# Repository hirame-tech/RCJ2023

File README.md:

# README規則
- 基板のバージョンごとの変更点、issue等はboard内の各基板フォルダに書く
- その他仕様等はプログラムが保存されているフォルダ内の一番上の階層に配置されたREADMEに記述する。

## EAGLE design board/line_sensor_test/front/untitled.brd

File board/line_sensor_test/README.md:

## v1 memo
- U1 0~15
- U2 16~29

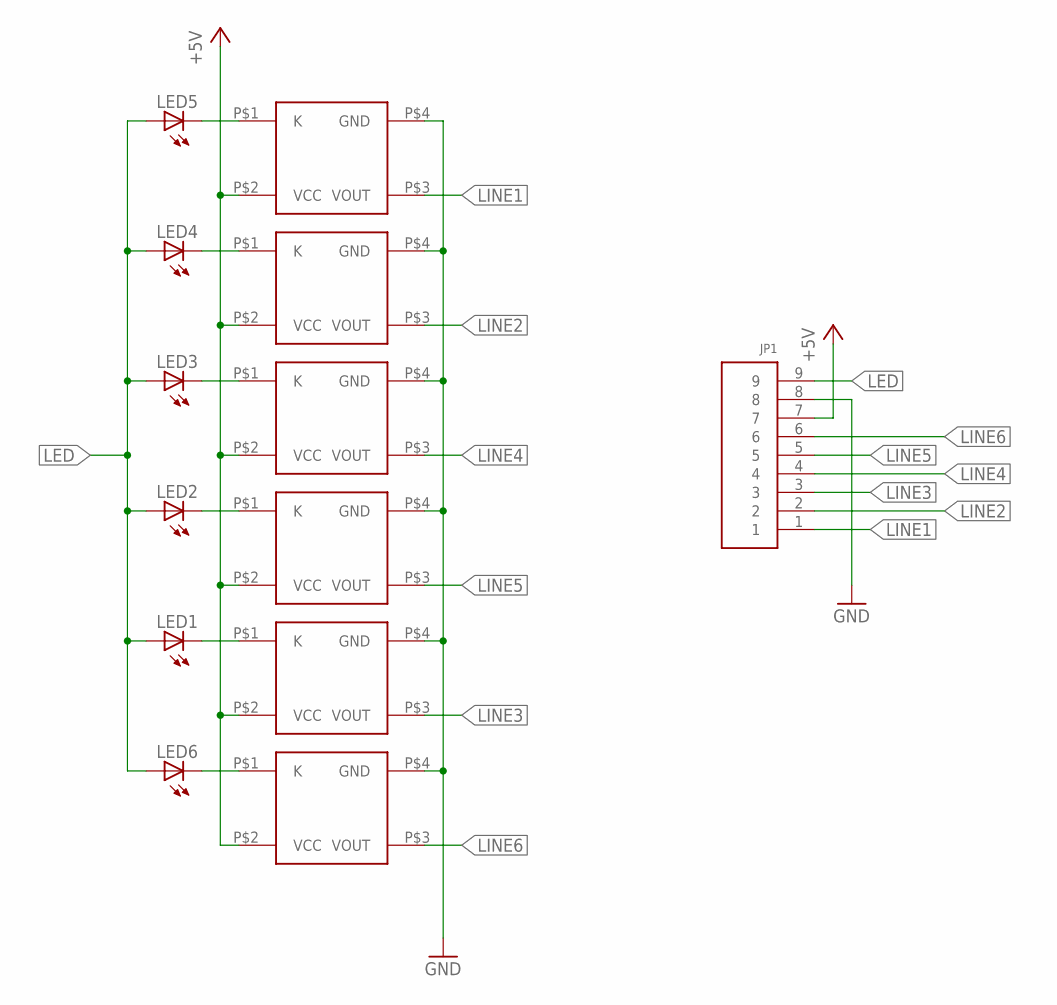
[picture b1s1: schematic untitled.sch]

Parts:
JP1: 9PIN; B9B-PH-K-S
LED1, LED2, LED3, LED4, LED5, LED6: LED5MM
U$1, U$2, U$3, U$4, U$5, U$6: S4282-51

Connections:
+5V: JP1.7, U$1.P$2 (VCC), U$2.P$2 (VCC), U$3.P$2 (VCC), U$4.P$2 (VCC), U$5.P$2 (VCC), U$6.P$2 (VCC)
GND: JP1.8, U$1.P$4 (GND), U$2.P$4 (GND), U$3.P$4 (GND), U$4.P$4 (GND), U$5.P$4 (GND), U$6.P$4 (GND)
LED: JP1.9, LED1.A, LED2.A, LED3.A, LED4.A, LED5.A, LED6.A
LINE1: JP1.1, U$1.P$3 (VOUT)
LINE2: JP1.2, U$2.P$3 (VOUT)
LINE3: JP1.3, U$5.P$3 (VOUT)
LINE4: JP1.4, U$3.P$3 (VOUT)
LINE5: JP1.5, U$4.P$3 (VOUT)
LINE6: JP1.6, U$6.P$3 (VOUT)
unnamed: LED5.K (C), U$1.P$1 (K)
unnamed: LED4.K (C), U$2.P$1 (K)
unnamed: LED3.K (C), U$3.P$1 (K)
unnamed: LED2.K (C), U$4.P$1 (K)
unnamed: LED1.K (C), U$5.P$1 (K)
unnamed: LED6.K (C), U$6.P$1 (K)

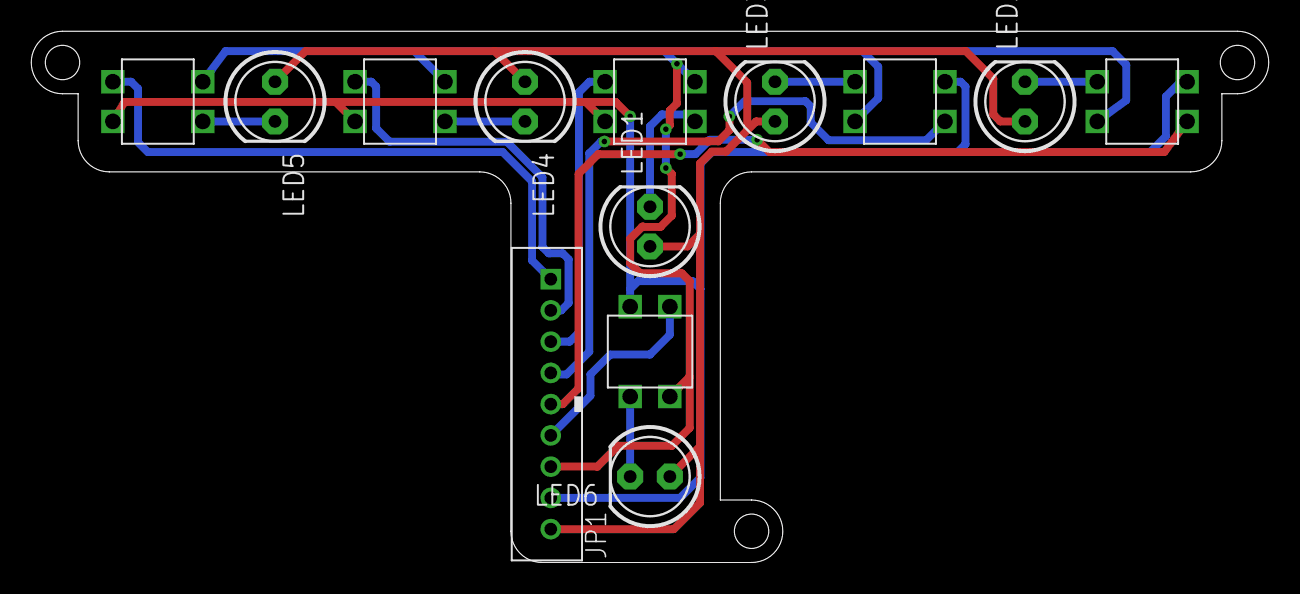
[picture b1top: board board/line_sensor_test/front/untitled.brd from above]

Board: 2 copper layers, 79.2 x 34.0 mm, 13 parts (0 on the bottom side), 15 nets.

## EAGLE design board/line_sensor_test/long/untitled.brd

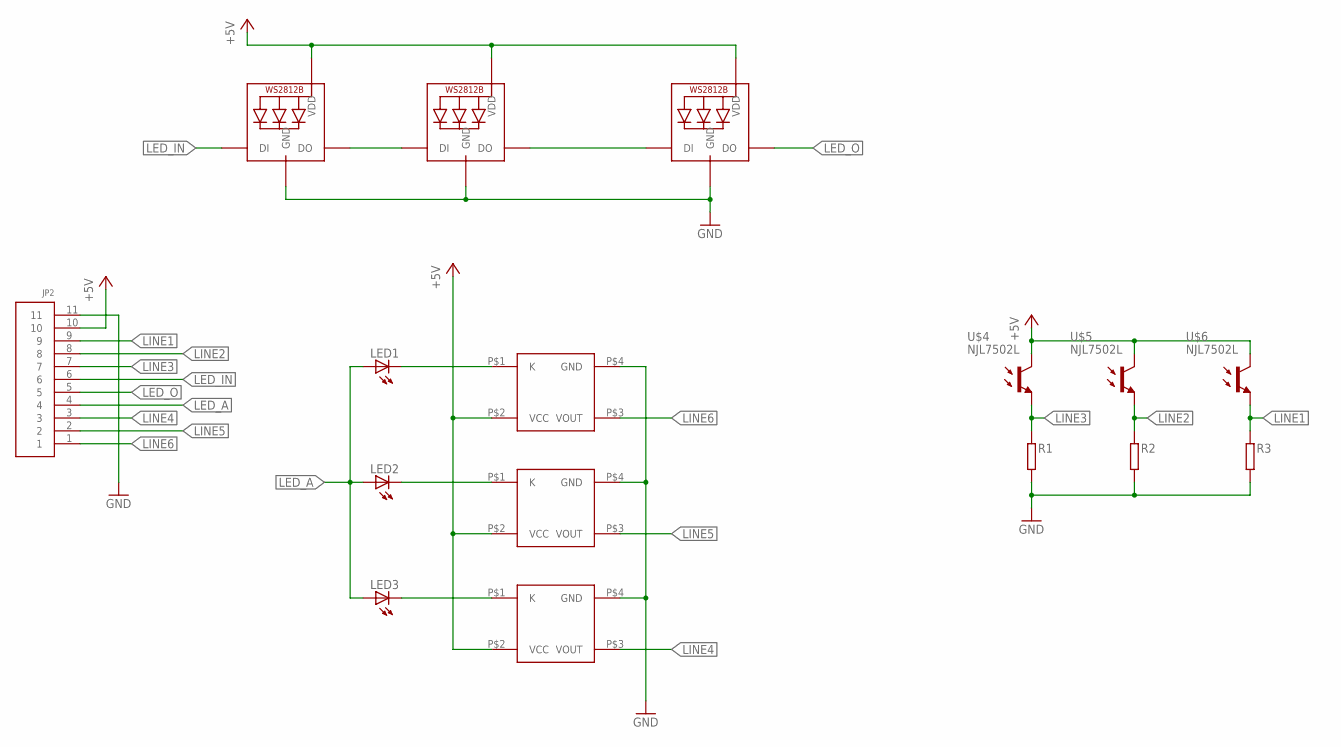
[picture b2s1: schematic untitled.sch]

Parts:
JP2: 11PIN; B11B-PH-K-S
LED1, LED2, LED3: LED5MM
LED4, LED5, LED6: WS2812B_5050N; WS2812B-NARROW
R1, R2, R3: RESISTOR1608; SMD1608
U$1, U$2, U$3: S4282-51
U$4, U$5, U$6: NJL7502L

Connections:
+5V: JP2.10, LED4.1-VDD (VDD), LED5.1-VDD (VDD), LED6.1-VDD (VDD), U$1.P$2 (VCC), U$2.P$2 (VCC), U$3.P$2 (VCC), U$4.C, U$5.C, U$6.C
GND: JP2.11, LED4.3-GND (GND), LED5.3-GND (GND), LED6.3-GND (GND), R1.2, R2.2, R3.2, U$1.P$4 (GND), U$2.P$4 (GND), U$3.P$4 (GND)
LED_A: JP2.4, LED1.A, LED2.A, LED3.A
LED_IN: JP2.6, LED6.4-DIN (DI)
LED_O: JP2.5, LED4.2-DOUT (DO)
LINE1: JP2.9, R3.1, U$6.E
LINE2: JP2.8, R2.1, U$5.E
LINE3: JP2.7, R1.1, U$4.E
LINE4: JP2.3, U$3.P$3 (VOUT)
LINE5: JP2.2, U$2.P$3 (VOUT)
LINE6: JP2.1, U$1.P$3 (VOUT)
unnamed: LED1.K (C), U$1.P$1 (K)
unnamed: LED2.K (C), U$2.P$1 (K)
unnamed: LED3.K (C), U$3.P$1 (K)
unnamed: LED5.4-DIN (DI), LED6.2-DOUT (DO)
unnamed: LED4.4-DIN (DI), LED5.2-DOUT (DO)

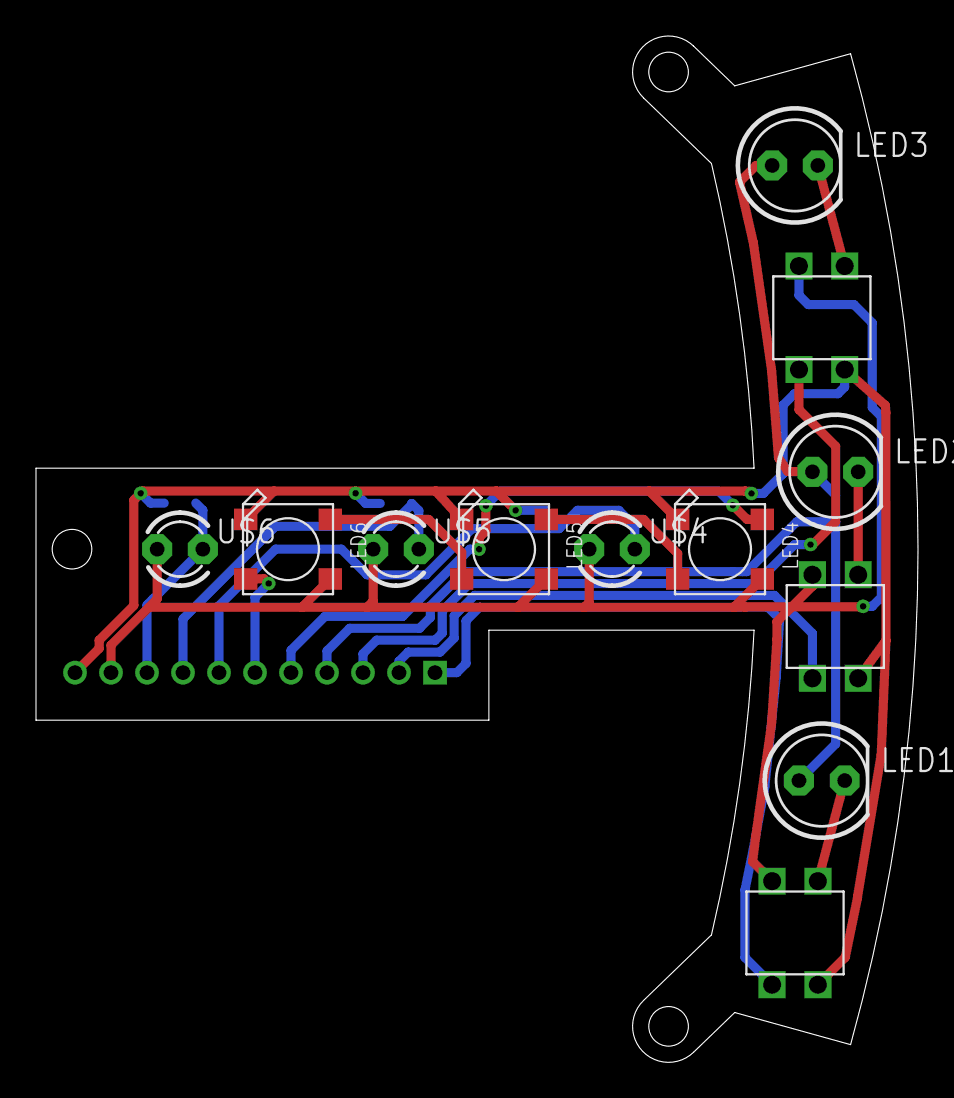
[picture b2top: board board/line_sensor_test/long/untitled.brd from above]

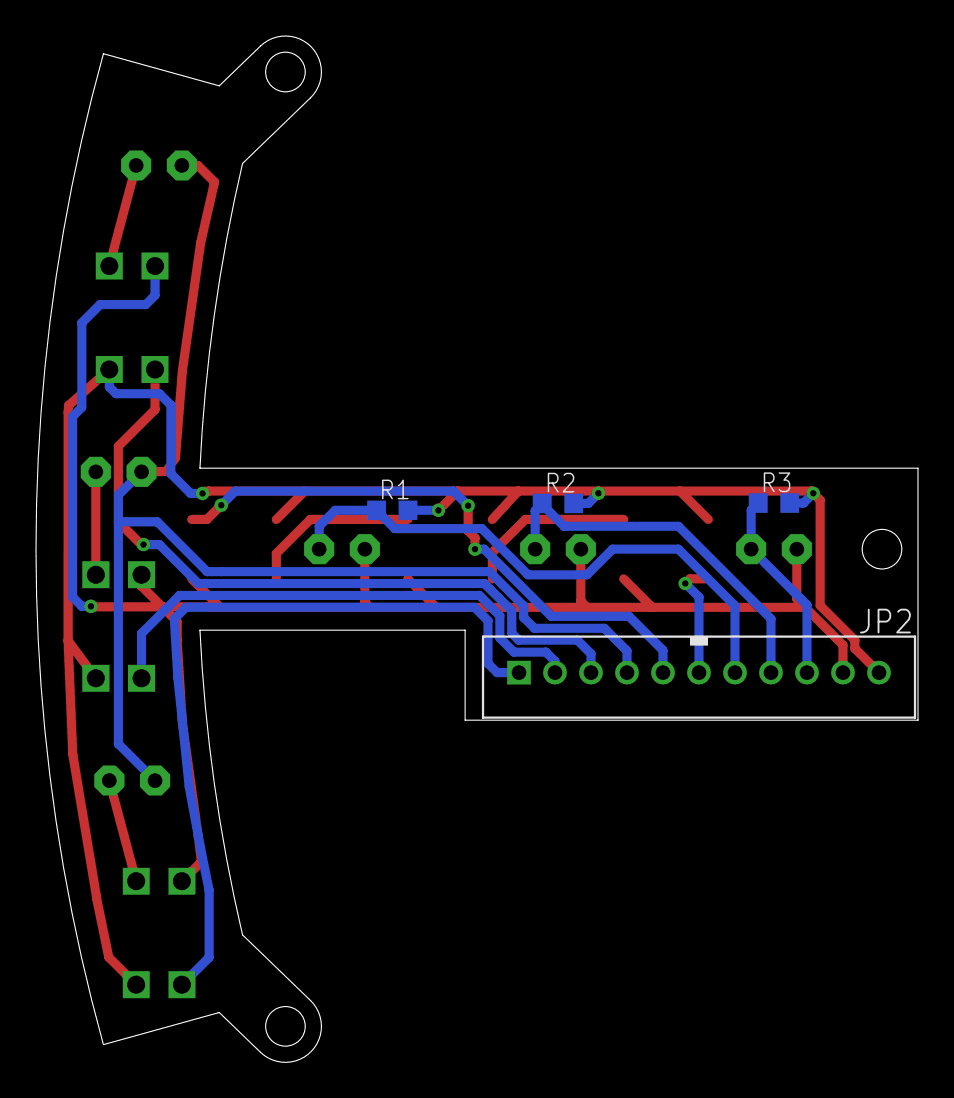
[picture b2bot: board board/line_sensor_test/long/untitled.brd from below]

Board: 2 copper layers, 49.0 x 57.0 mm, 16 parts (4 on the bottom side), 16 nets.

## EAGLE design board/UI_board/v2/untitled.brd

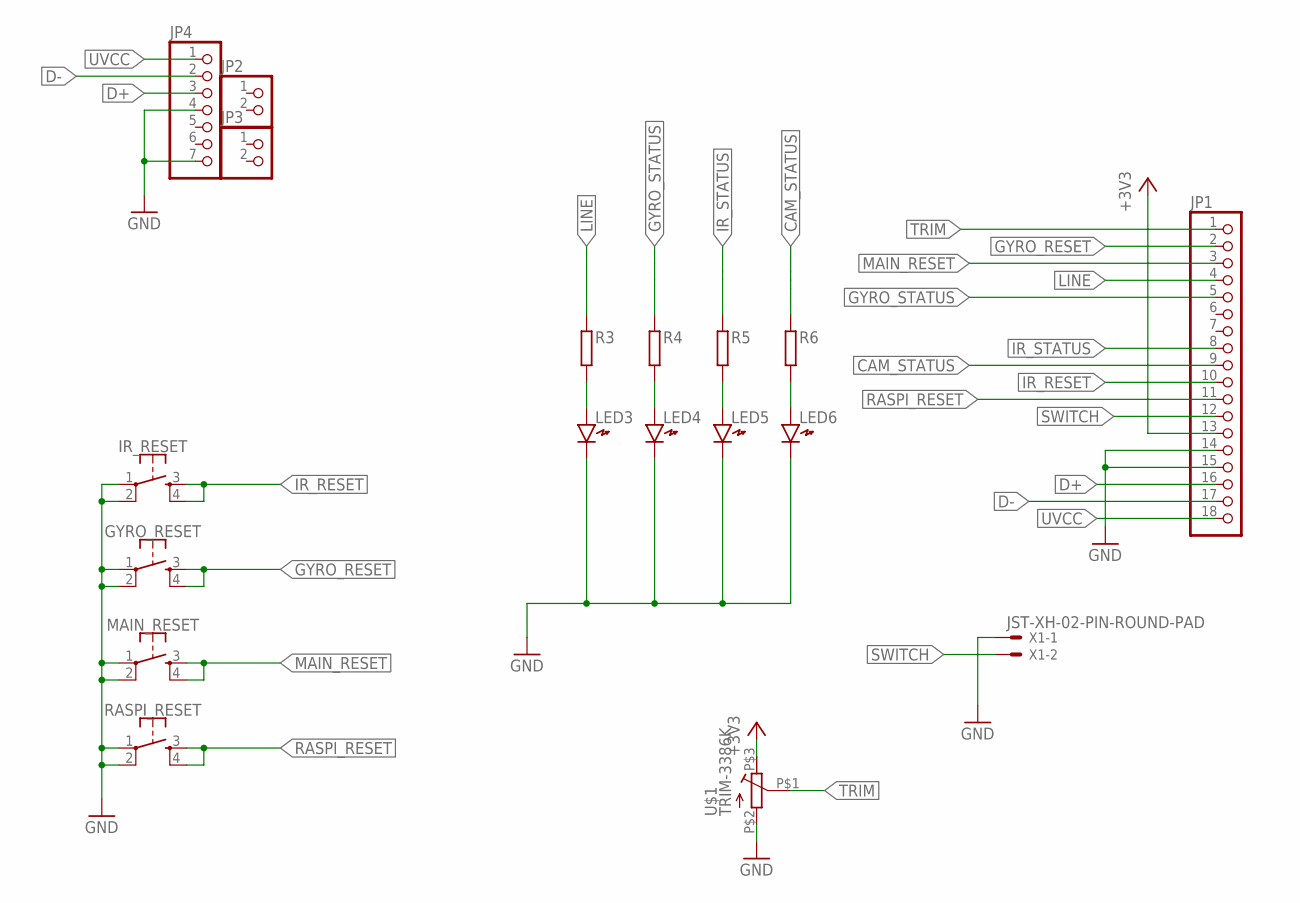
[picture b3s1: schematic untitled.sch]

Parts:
GYRO_RESET: MOMENTARY-SWITCH-SPST-2-SMD-5.2MM; TACTILE_SWITCH_SMD_5.2MM
IR_RESET: MOMENTARY-SWITCH-SPST-2-SMD-5.2MM; TACTILE_SWITCH_SMD_5.2MM
JP1: PINHD-1X18; 1X18
JP2, JP3: PINHD-1X2; 1X02
JP4: PINHD-1X7; 1X07
LED3, LED4, LED5, LED6: LED1608
MAIN_RESET: MOMENTARY-SWITCH-SPST-2-SMD-5.2MM; TACTILE_SWITCH_SMD_5.2MM
R3, R4, R5, R6: RESISTOR1608; SMD1608
RASPI_RESET: MOMENTARY-SWITCH-SPST-2-SMD-5.2MM; TACTILE_SWITCH_SMD_5.2MM
U$1: TRIM-3386K
X1: JST-XH-02-PIN-ROUND-PAD; JST-XH-02-PACKAGE-ROUND-PAD

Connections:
+3V3: JP1.13, U$1.P$3 (1)
CAM_STATUS: JP1.9, R6.1
D+: JP1.16, JP4.3
D-: JP1.17, JP4.2
GND: GYRO_RESET.1, GYRO_RESET.2, IR_RESET.1, IR_RESET.2, JP1.14, JP1.15, JP4.4, JP4.7, LED3.K, LED4.K, LED5.K, LED6.K, MAIN_RESET.1, MAIN_RESET.2, RASPI_RESET.1, RASPI_RESET.2, U$1.P$2 (2), X1.1
GYRO_RESET: GYRO_RESET.3, GYRO_RESET.4, JP1.2
GYRO_STATUS: JP1.5, R4.1
IR_RESET: IR_RESET.3, IR_RESET.4, JP1.10
IR_STATUS: JP1.8, R5.1
LINE: JP1.4, R3.1
MAIN_RESET: JP1.3, MAIN_RESET.3, MAIN_RESET.4
unnamed: LED3.A, R3.2
unnamed: LED4.A, R4.2
unnamed: LED5.A, R5.2
unnamed: LED6.A, R6.2
RASPI_RESET: JP1.11, RASPI_RESET.3, RASPI_RESET.4
SWITCH: JP1.12, X1.2
TRIM: JP1.1, U$1.P$1 (3)
UVCC: JP1.18, JP4.1

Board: 2 copper layers, 18 parts (0 on the bottom side), 19 nets, no tracks yet.

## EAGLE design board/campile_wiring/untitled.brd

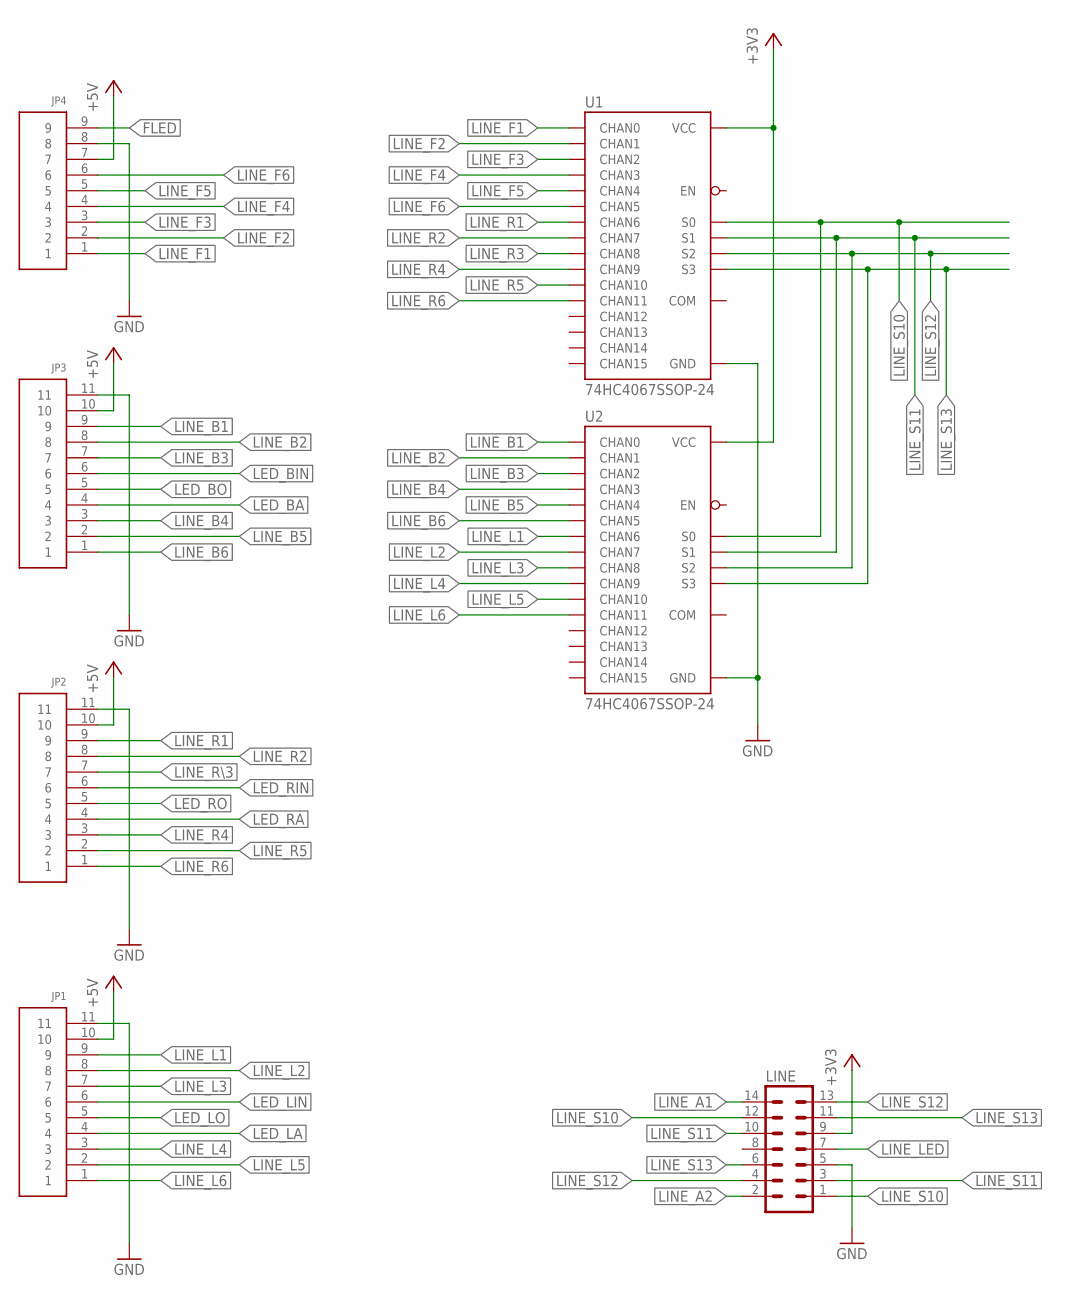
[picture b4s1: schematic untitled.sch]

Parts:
JP1, JP2, JP3: 11PIN; B11B-PH-K-S
JP4: 9PIN; B9B-PH-K-S
LINE: MA07-2
U1, U2: 74HC4067SSOP-24; SSOP24

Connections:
+3V3: LINE.9, U1.24 (VCC), U2.24 (VCC)
+5V: JP1.10, JP2.10, JP3.10, JP4.7
FLED: JP4.9
GND: JP1.11, JP2.11, JP3.11, JP4.8, LINE.5, U1.12 (GND), U2.12 (GND)
LED_BA: JP3.4
LED_BIN: JP3.6
LED_BO: JP3.5
LED_LA: JP1.4
LED_LIN: JP1.6
LED_LO: JP1.5
LED_RA: JP2.4
LED_RIN: JP2.6
LED_RO: JP2.5
LINE_A1: LINE.14
LINE_A2: LINE.2
LINE_B1: JP3.9, U2.9 (CHAN0)
LINE_B2: JP3.8, U2.8 (CHAN1)
LINE_B3: JP3.7, U2.7 (CHAN2)
LINE_B4: JP3.3, U2.6 (CHAN3)
LINE_B5: JP3.2, U2.5 (CHAN4)
LINE_B6: JP3.1, U2.4 (CHAN5)
LINE_F1: JP4.1, U1.9 (CHAN0)
LINE_F2: JP4.2, U1.8 (CHAN1)
LINE_F3: JP4.3, U1.7 (CHAN2)
LINE_F4: JP4.4, U1.6 (CHAN3)
LINE_F5: JP4.5, U1.5 (CHAN4)
LINE_F6: JP4.6, U1.4 (CHAN5)
LINE_L1: JP1.9, U2.3 (CHAN6)
LINE_L2: JP1.8, U2.2 (CHAN7)
LINE_L3: JP1.7, U2.23 (CHAN8)
LINE_L4: JP1.3, U2.22 (CHAN9)
LINE_L5: JP1.2, U2.21 (CHAN10)
LINE_L6: JP1.1, U2.20 (CHAN11)
LINE_LED: LINE.7
LINE_R1: JP2.9, U1.3 (CHAN6)
LINE_R2: JP2.8, U1.2 (CHAN7)
LINE_R3: U1.23 (CHAN8)
LINE_R4: JP2.3, U1.22 (CHAN9)
LINE_R5: JP2.2, U1.21 (CHAN10)
LINE_R6: JP2.1, U1.20 (CHAN11)
LINE_R\3: JP2.7
LINE_S10: LINE.1, LINE.12, U1.10 (S0), U2.10 (S0)
LINE_S11: LINE.3, LINE.10, U1.11 (S1), U2.11 (S1)
LINE_S12: LINE.4, LINE.13, U1.14 (S2), U2.14 (S2)
LINE_S13: LINE.6, LINE.11, U1.13 (S3), U2.13 (S3)

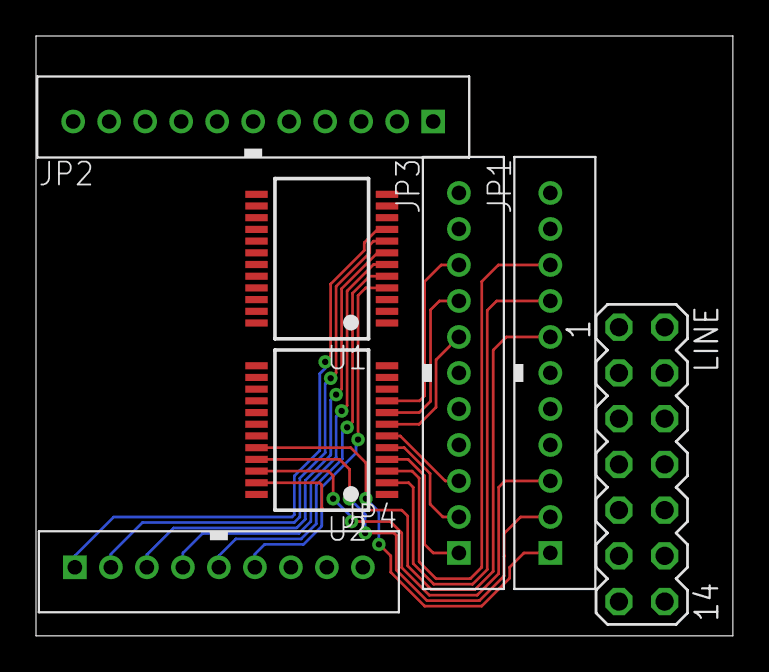
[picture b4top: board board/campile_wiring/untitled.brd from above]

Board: 2 copper layers, 38.7 x 33.3 mm, 7 parts (0 on the bottom side), 30 nets.

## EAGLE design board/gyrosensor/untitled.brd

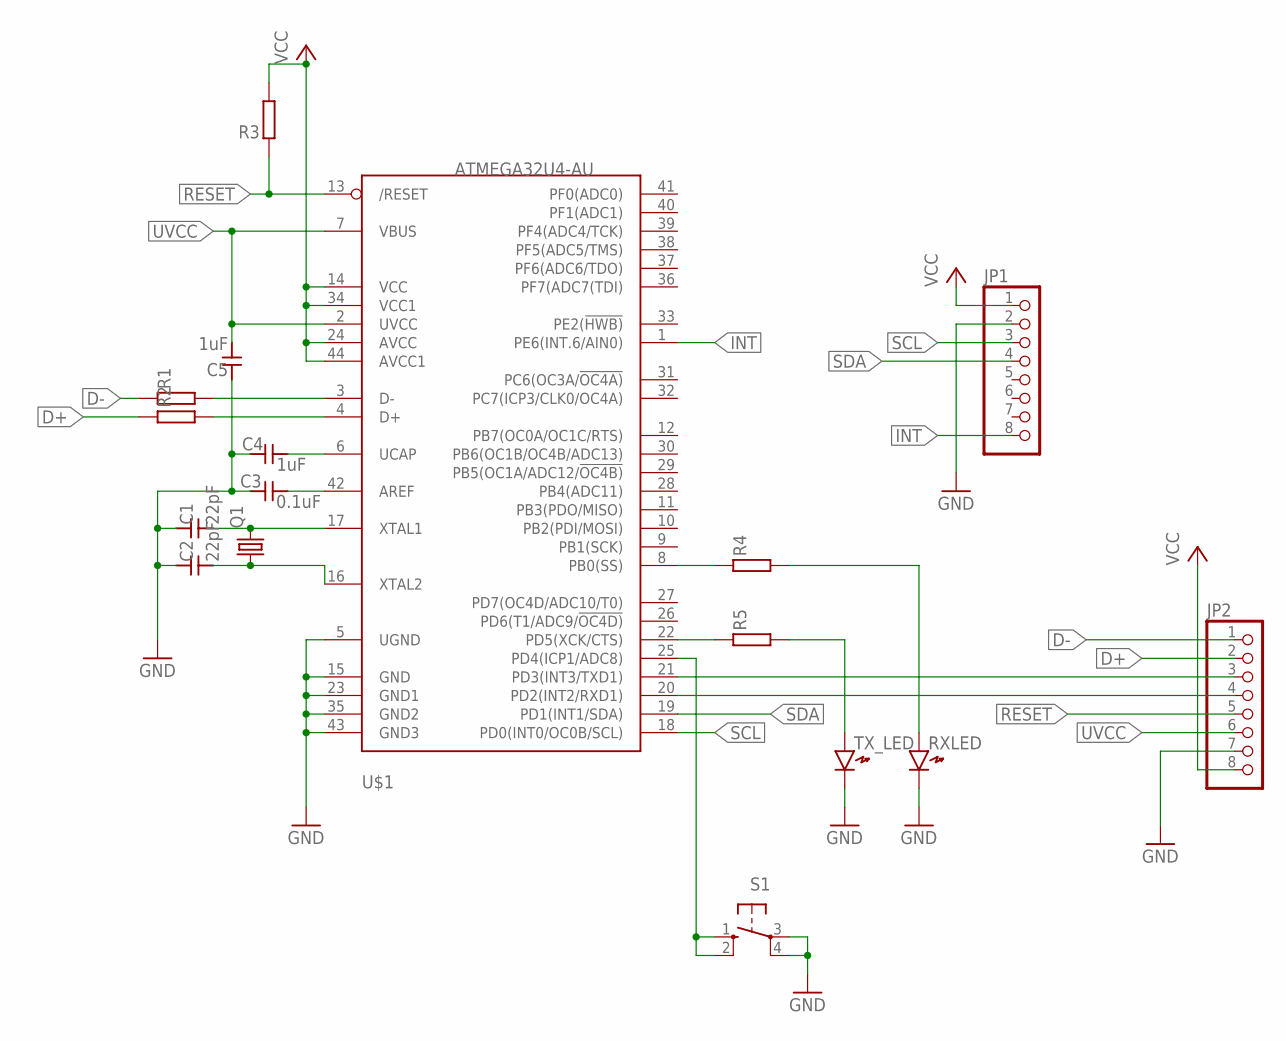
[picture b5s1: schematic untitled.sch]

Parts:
C1, C2: 22pF; SMD1608
C3: 0.1uF; SMD1608
C4, C5: 1uF; SMD1608
JP1, JP2: PINHD-1X8; 1X08
Q1: CRYSTALHC49S; HC49/S
R1, R2, R3, R4, R5: RESISTOR1608; SMD1608
RXLED: LED1608
S1: 10-XX; B3F-10XX
TX_LED: LED1608
U$1: ATMEGA32U4-AU; TQFP44

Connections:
D+: JP2.2, R2.1
D-: JP2.1, R1.1
GND: C1.1, C2.1, C3.1, C4.1, C5.1, JP1.2, JP2.7, RXLED.K, S1.3, S1.4 (P1), TX_LED.K, U$1.5 (UGND), U$1.15 (GND), U$1.23 (GND1), U$1.35 (GND2), U$1.43 (GND3)
INT: JP1.8, U$1.1 (PE6(INT.6/AIN0))
unnamed: C1.2, Q1.2, U$1.17 (XTAL1)
unnamed: C2.2, Q1.1, U$1.16 (XTAL2)
unnamed: C4.2, U$1.6 (UCAP)
unnamed: C3.2, U$1.42 (AREF)
unnamed: S1.1 (S), S1.2 (S1), U$1.25 (PD4(ICP1/ADC8))
unnamed: R4.1, U$1.8 (PB0(SS))
unnamed: R5.1, U$1.22 (PD5(XCK/CTS))
unnamed: R1.2, U$1.3 (D-)
unnamed: R2.2, U$1.4 (D+)
unnamed: R5.2, TX_LED.A
unnamed: R4.2, RXLED.A
unnamed: JP2.3, U$1.21 (PD3(INT3/TXD1))
unnamed: JP2.4, U$1.20 (PD2(INT2/RXD1))
RESET: JP2.5, R3.1, U$1.13 (/RESET)
SCL: JP1.3, U$1.18 (PD0(INT0/OC0B/SCL))
SDA: JP1.4, U$1.19 (PD1(INT1/SDA))
UVCC: C5.2, JP2.6, U$1.2 (UVCC), U$1.7 (VBUS)
VCC: JP1.1, JP2.8, R3.2, U$1.14 (VCC), U$1.24 (AVCC), U$1.34 (VCC1), U$1.44 (AVCC1)

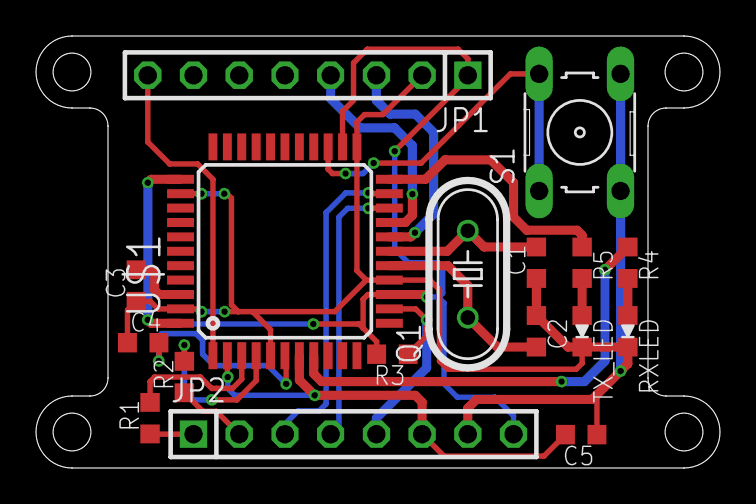
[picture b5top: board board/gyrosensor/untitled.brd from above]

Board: 2 copper layers, 38.0 x 24.0 mm, 17 parts (0 on the bottom side), 22 nets.

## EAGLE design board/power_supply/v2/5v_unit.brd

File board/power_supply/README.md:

## power supply board v1
- OKLを手はんだに対応させた方がいいのでは？
- ヒューズの長さが違う

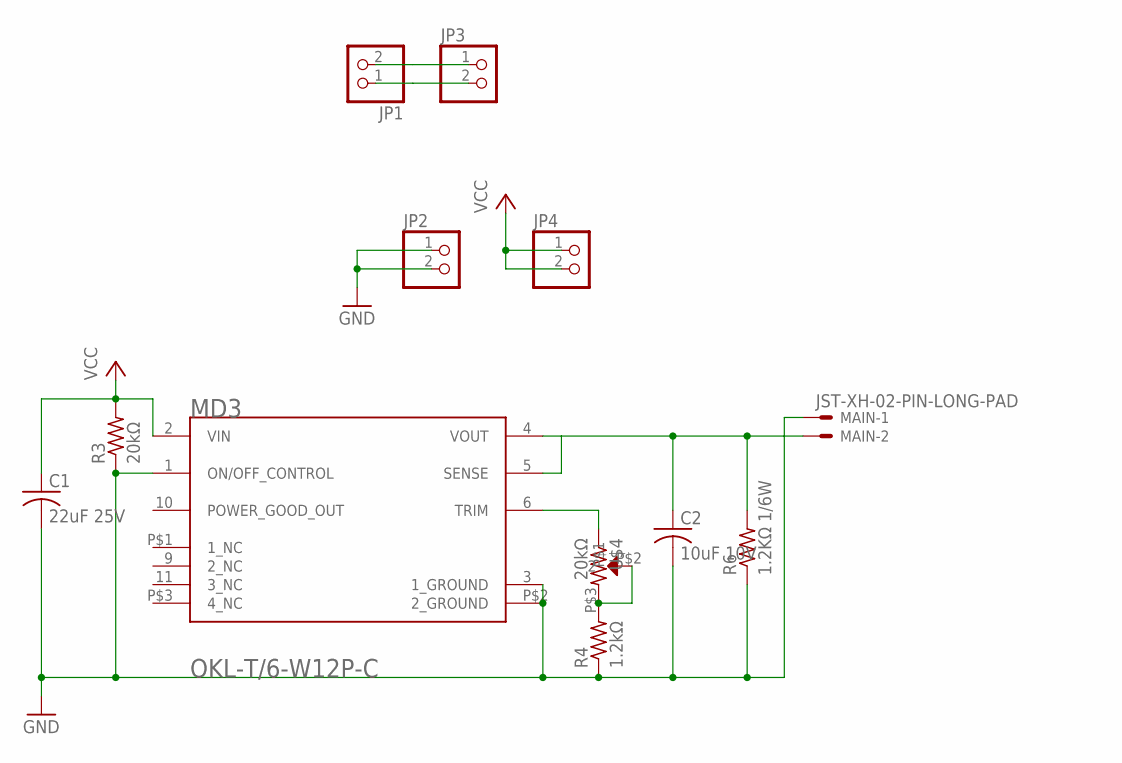
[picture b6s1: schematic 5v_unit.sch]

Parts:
C1: 22uF 25V; C2012
C2: 10uF 10V; C2012
JP1, JP2, JP3, JP4: PINHD-1X2; 1X02
MAIN: JST-XH-02-PIN-LONG-PAD; JST-XH-02-PACKAGE-LONG-PAD
MD3: OKL-T/6-W12P-CMURATA_OKL-T-6-W12P-C_0_0; MURATA_OKL-T-6-W12P-C_0
R3: 20kΩ; M2012
R4: 1.2kΩ; M2012
R6: 1.2KΩ 1/6W; 0805-THM
U$4: 20kΩ; R-TRIM

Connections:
GND: C1.2, C2.2, JP2.1, JP2.2, MAIN.1, MD3.1 (ON/OFF_CONTROL), MD3.3 (1_GROUND), MD3.P$2 (2_GROUND), R3.1, R4.1, R6.1
unnamed: JP1.1, JP1.2, JP3.1, JP3.2
unnamed: R4.2, U$4.P$2 (2), U$4.P$3
unnamed: C2.1, MAIN.2, MD3.4 (VOUT), MD3.5 (SENSE), R6.2
unnamed: MD3.6 (TRIM), U$4.P$1 (1)
VCC: C1.1, JP4.1, JP4.2, MD3.2 (VIN), R3.2

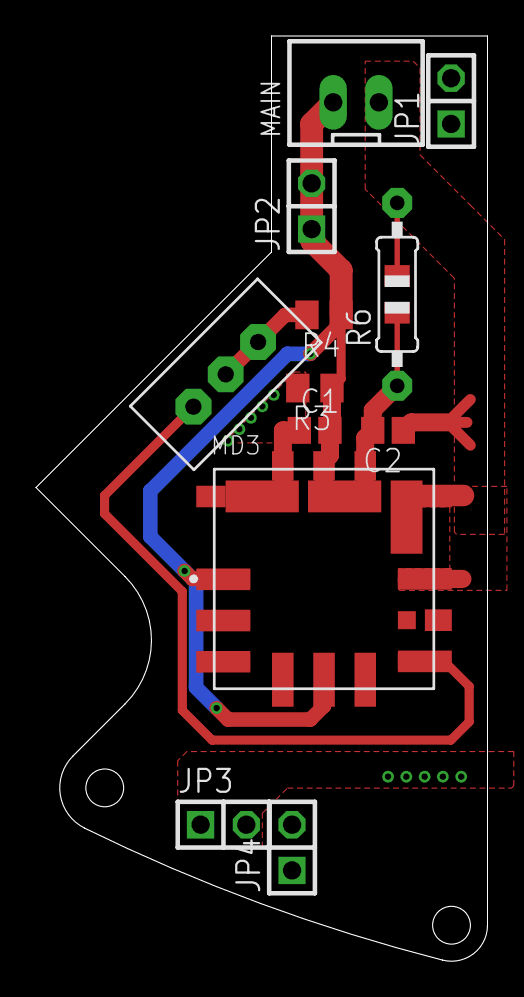
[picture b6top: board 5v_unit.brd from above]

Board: 2 copper layers, 25.1 x 51.4 mm, 12 parts (0 on the bottom side), 6 nets.

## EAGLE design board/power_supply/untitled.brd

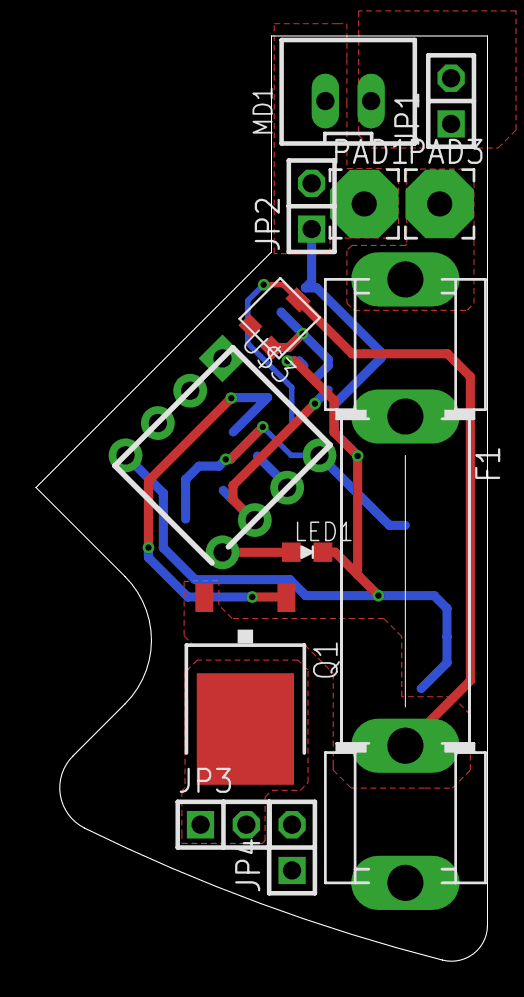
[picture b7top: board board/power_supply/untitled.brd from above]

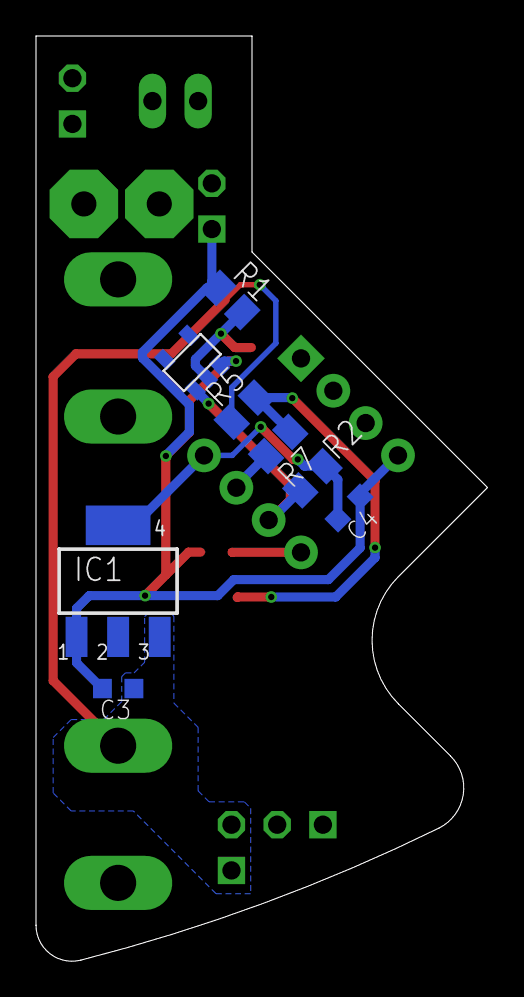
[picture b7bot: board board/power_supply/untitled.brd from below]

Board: 2 copper layers, 25.1 x 51.4 mm, 20 parts (8 on the bottom side), 11 nets.

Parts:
C3, C4: 0.1uF; SMD1608
F1: SH32
IC1: 317EMP; SOT223
JP1, JP2, JP3, JP4: 1X02
LED1: LED1608
MD1: JST-XH-02-PIN-LONG-PAD; JST-XH-02-PACKAGE-LONG-PAD
PAD1, PAD3: 3,81/1,4
Q1: FDD4141TO252; TO252
R1, R7: 300Ω; M2012
R2: 470kΩ; M2012
R5: 10k; M2012
U$1: R3111N211A
U$2: 2.2kΩ; SMD-R-TRIM
U$3: ATTINY85; 8P3

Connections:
GND: C3.2, C4.1, IC1.1, JP2.1, JP2.2, LED1.K, MD1.1, PAD1.1, R1.1, U$1.P$2, U$3.4
unnamed: R1.2, U$1.P$1, U$2.P$1
unnamed: Q1.1, R5.2, R7.1
unnamed: F1.1A, PAD3.1
unnamed: R2.1, U$1.P$3, U$3.6
unnamed: JP3.1, JP3.2, Q1.3
unnamed: LED1.A, U$3.5
unnamed: JP1.1, JP1.2, MD1.2
unnamed: R7.2, U$3.7
unnamed: C4.2, IC1.4, R2.2, U$3.8
VCC: C3.1, F1.2A, IC1.3, JP4.1, JP4.2, Q1.2, R5.1, U$2.P$3

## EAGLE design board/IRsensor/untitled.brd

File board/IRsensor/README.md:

## v1_issure
- ~左のIRが上に1mmずれてる~ v1内で修正済み
- SPI引き出し忘れ

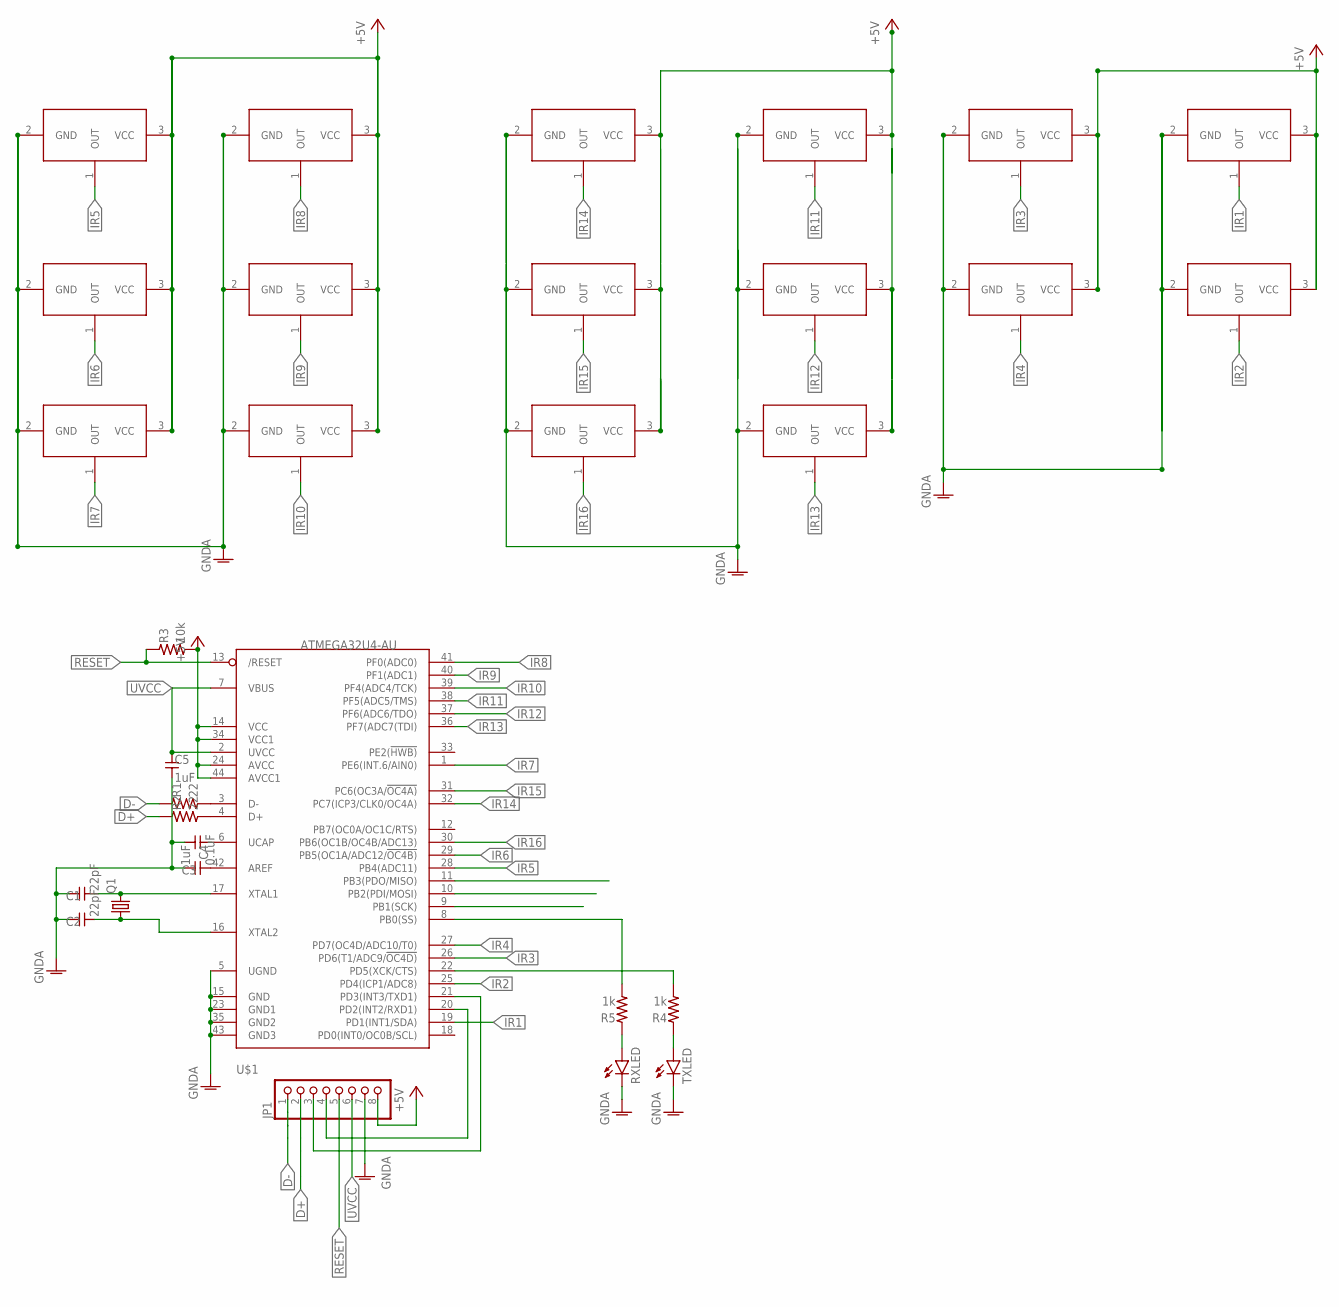
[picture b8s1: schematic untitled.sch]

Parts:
C1, C2: 22pF; SMD1608
C3: 0.1uF; SMD1608
C4, C5: 1uF; SMD1608
IR1, IR2, IR3, IR4, IR5, IR6, IR7, IR8, IR9, IR10, IR11, IR12, IR13, IR14, IR15, IR16: IRM2121-A538; IRM_V
JP1: PINHD-1X8BIG; 1X08-BIG
Q1: CRYSTALHC49S; HC49/S
R1, R2: 22; SMD1608
R3: 10k; SMD1608
R4, R5: 1k; SMD1608
RXLED: LEDSML0603; SML0603
TXLED: LEDSML0603; SML0603
U$1: ATMEGA32U4-AU; TQFP44

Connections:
+5V: IR1.3 (VCC), IR2.3 (VCC), IR3.3 (VCC), IR4.3 (VCC), IR5.3 (VCC), IR6.3 (VCC), IR7.3 (VCC), IR8.3 (VCC), IR9.3 (VCC), IR10.3 (VCC), IR11.3 (VCC), IR12.3 (VCC), IR13.3 (VCC), IR14.3 (VCC), IR15.3 (VCC), IR16.3 (VCC), JP1.8, R3.2, U$1.14 (VCC), U$1.24 (AVCC), U$1.34 (VCC1), U$1.44 (AVCC1)
D+: JP1.2, R2.1
D-: JP1.1, R1.1
GNDA: C1.1, C2.1, C3.1, C4.2, C5.2, IR1.2 (GND), IR2.2 (GND), IR3.2 (GND), IR4.2 (GND), IR5.2 (GND), IR6.2 (GND), IR7.2 (GND), IR8.2 (GND), IR9.2 (GND), IR10.2 (GND), IR11.2 (GND), IR12.2 (GND), IR13.2 (GND), IR14.2 (GND), IR15.2 (GND), IR16.2 (GND), JP1.7, RXLED.C, TXLED.C, U$1.5 (UGND), U$1.15 (GND), U$1.23 (GND1), U$1.35 (GND2), U$1.43 (GND3)
IR1: IR1.1 (OUT), U$1.19 (PD1(INT1/SDA))
IR2: IR2.1 (OUT), U$1.25 (PD4(ICP1/ADC8))
IR3: IR3.1 (OUT), U$1.26 (PD6(T1/ADC9/!OC4D))
IR4: IR4.1 (OUT), U$1.27 (PD7(OC4D/ADC10/T0))
IR5: IR5.1 (OUT), U$1.28 (PB4(ADC11))
IR6: IR6.1 (OUT), U$1.29 (PB5(OC1A/ADC12/!OC4B))
IR7: IR7.1 (OUT), U$1.1 (PE6(INT.6/AIN0))
IR8: IR8.1 (OUT), U$1.41 (PF0(ADC0))
IR9: IR9.1 (OUT), U$1.40 (PF1(ADC1))
IR10: IR10.1 (OUT), U$1.39 (PF4(ADC4/TCK))
IR11: IR11.1 (OUT), U$1.38 (PF5(ADC5/TMS))
IR12: IR12.1 (OUT), U$1.37 (PF6(ADC6/TDO))
IR13: IR13.1 (OUT), U$1.36 (PF7(ADC7(TDI))
IR14: IR14.1 (OUT), U$1.32 (PC7(ICP3/CLK0/OC4A))
IR15: IR15.1 (OUT), U$1.31 (PC6(OC3A/!OC4A))
IR16: IR16.1 (OUT), U$1.30 (PB6(OC1B/OC4B/ADC13))
unnamed: JP1.4, U$1.20 (PD2(INT2/RXD1))
unnamed: JP1.3, U$1.21 (PD3(INT3/TXD1))
unnamed: C3.2, U$1.42 (AREF)
unnamed: C4.1, U$1.6 (UCAP)
unnamed: C1.2, Q1.2, U$1.17 (XTAL1)
unnamed: C2.2, Q1.1, U$1.16 (XTAL2)
unnamed: R1.2, U$1.3 (D-)
unnamed: R2.2, U$1.4 (D+)
unnamed: R4.2, U$1.22 (PD5(XCK/CTS))
unnamed: R4.1, TXLED.A
unnamed: R5.1, RXLED.A
unnamed: R5.2, U$1.8 (PB0(SS))
RESET: JP1.5, R3.1, U$1.13 (/RESET)
UVCC: C5.1, JP1.6, U$1.2 (UVCC), U$1.7 (VBUS)

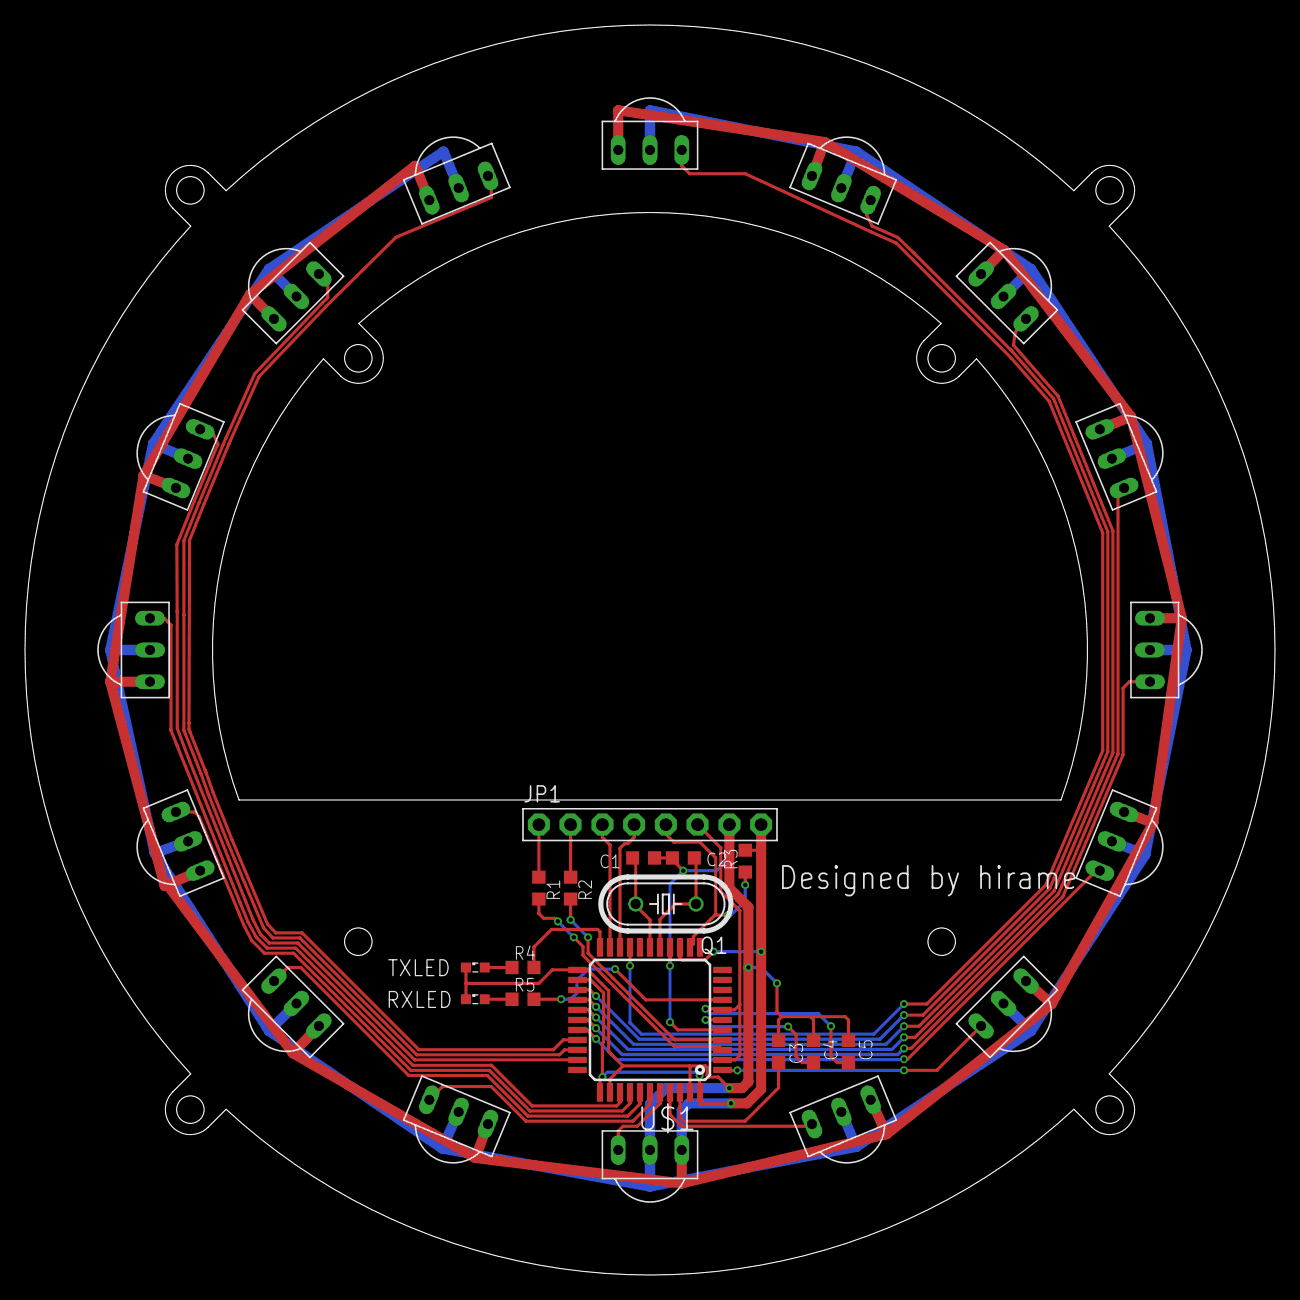
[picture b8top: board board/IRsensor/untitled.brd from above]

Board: 2 copper layers, 100.0 x 100.0 mm, 31 parts (0 on the bottom side), 34 nets.

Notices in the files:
parts and their libraries:
SparkFun-Switches: Licensing: Creative Commons ShareAlike 4.0 International - https://creativecommons.org/licenses/by-sa/4.0
